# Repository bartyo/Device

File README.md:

# Device Work & Study Repository

This repository is a cluster of all work and studies concerning the wearable device of th Follow.ER project.

*Currently into this repository :*

- Prototype design an testing

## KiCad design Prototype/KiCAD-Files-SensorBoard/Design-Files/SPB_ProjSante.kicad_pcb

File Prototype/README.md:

# Prototype

## Current Status
Building the Adafruit nRF52 base code / Check the SPB solders

## Summary

This folder contains the files and studies that have been made to build a prototype design of the wearable device.

+ Follow.ER Goals
+ Global Architecture
+ Device Architecture
+ Device Prototype Goals
+ Elements
  + The MCU
  + The Sensors HUB

## Follow.ER Goals

 Follow.ER is a project that wants to build an easy patients-monitoring system for the ER thanks to wearable devices following thoses rules :
 
 - Able to follow Oximetry , HeartBeat and Localisation  (+ optionnal data)
 - Easy to Use
 - Safe
 - Costless

## Global Architecture

The Follow.ER system consist of wearables devices following patients in a mesh-designed BLE network. This allow centralized server management, distant access to data trough a WebApp and patient localisation (by BLE meshing & proximity)

## Device Architecture

The device system is a wearable sensor hub dedicated to Oximetry and Heartbeat measurement (+ optionnal Temperature or Movements). The system should be able to transmit trustful data, alarms and identifications thanks to the [BLE protocol]() in a secure way (ex: crypto).

## Device Prototype Goals

Before strating the "industry compatible" final designs, we need to be able to build a Proof of Concept to ensure that all the things we want to deploy is possible to realise. And so :

 - Being able to gather oximetry and pulse form transmissive or reflective measurement
 - Being able to tramsit data via BLE in a secure way 
 - Reach a current consumption level compatible with a wearable device

## Elements

The Device Prototype System (DPS) is make of two elements :

 - A MCU able to transmit trought BLE
 - A sensors HUB board able to return the targeted data and more if needed. 
 
 This system could be displayed as :

### The MCU => Feather nRF52 BlueFruit LE (Adafruit BLE)

The Feather nRF52 Bluefruit LE , from Adafruit Industires have been choosen because it allow to deploy an embedded BLE solution in a simple way (Arduino IDE compatible + breadboard pinout).

#### Board PinOut

The board PinOut can be found [HERE](https://learn.adafruit.com/bluefruit-nrf52-feather-learning-guide/device-pinout)

> The pin attributions could be found into the code and can be easily changed.

#### Protoype Code Architecure

The Prototype Code is based on a "TOKEN" system.

The user, via BLE or UART will send a 3 letters TOKEN that will tell the MCU the action to perform.
For exemple, ``BLK`` will cause the built-in red led to blink 5 time for 2,5s (a token table is indicated in the code and later in the docs).

That system allow an user to simply test methods and functions thanks to single instructions. Consequently, the softawre is constantly waiting for new tokens to follow. 

If a wrong token or an other situation trigger an error (variable ``done`` == ``false`` ), the system will send a message trough the selected communication protocol and set the token as ``NOP`` (do nothing) so user action can block the MCU.

Here's the architecture :

And here's the ***current*** TOKEN table (add new one if needed):

|TOKEN|Action|Need to send opt. Data ?|
|:--:|:--:|:--:|
|``NOP``|Do nothing| No |
|``ERR``|Raise an error (test func)| No |
|``BLK``|Do nothing| No |
|``OXI``|Gather Oximetry Data (single)| No |
|``OXB``|Gather Oximetry Data (buffered)| No |
|``TMP``|Gather Die Temperature| No |
|``MOD``|Switch the communication mode (BLE/UART)| No |
|``HWP``|Switch the hardawre interaction mode (SIMULATED/GPIOs)| No |
|``PTS``|Set the number of point to gather in buffered mode| Yes (16bit HEXA, ex: AF55)|
|``SMP``|Set the chip sampling frequency| Yes (8bit HEXA, ex: F5)|
|``AMP``|Set the chip range| Yes (8bit HEXA, ex: 08)|
|``PUL``|Set the chip pulse width| Yes (8bit HEXA, ex: A3)|
|``INT``|Set the chip/led current consumption| Yes (8bit HEXA, ex: 30)|

> For the Hexa values, look at the MAX30101 datasheet :) (the soft should take care of the rest)

An exemple of UART prototyping control:

### The Sensors HUB => Sensor Prototype Board (SPB)

To allow us to prototype with oximetry measurement, **we've built a Sensors Prototype Board** that gather **oximetry signal** by **reflectance method**. The chip is also able to send **die temperature measurements**.

In addition, we choose to put **two current measurement channels** so we should be able to **plot consumption curves** during the system study and reach better programming solution if needed.

Of course, the eletronical environnement is designed for a bug free use (I2C pull-up , decoupling resistors, voltage regulation, etc..)

The board B.O.M and the GERBER files could be found [HERE](https://github.com/ProjSante/Device/tree/master/Prototype/KiCAD-Files-SensorBoard)

The simplified board architecture could be displayed as :

#### SPB PinOut

> /!\ The input voltage should be 3.3v if you just want to use the Red and the IR LED; 5v if you want to use the Red, the IR and the Green LED

> Current measurement : Current_Analog or Current_Digital (in Volts) / 2000 =** ***Real Current*** (ex: 1V == 0.5mA)

To avoid ESB hazards, a protection could be put over the board thanks to the 4 fixation holes :

#### I2C methods

See the [MAX30101 Datasheet](https://datasheets.maximintegrated.com/en/ds/MAX30101.pdf)

|**Function**|Adress|Effects|Main Direction|
|:------:|:----:|:-----:|:-----:|
| Interrupt enable 1 | 0x02 | Use the bit 7 to 5 to set the interrupt conditions about dataflow | Write |
| Interrupt enable 2 | 0x03 | Use the bit 1 to set the interrupt condition about die temperature| Write |
| FIFO Write Pointer | 0x04 | Last data adress location , bytes 4 to 0 | Read |
| OF Counter | 0x05 | Overflow counter (if FIFO Full) , bytes 4 to 0 | Read |
| FIFO Read Pointer | 0x06 | I2C read adress location , bytes 4 to 0 | Read & Write |
| FIFO Data Register | 0x07 | Pointed data register (not always auto-incremented), 3x1 byte for one channel| Read |
| FIFO Config| 0x08 | Averaging [7:5] , FIFO RollOver Enable [4] , FIFO status when almost full [3:0] | Read & Write |
| Mode Config| 0x09 | Shutdown (register keeped and Int==0) [7] , Reset [6] , Measurement Mode [2:0] | Write |
| SpO2 Config| 0x0A | ADC Range [6:5] , Sample Rate [4:2] , Pulse Width [1:0] | Write |
| LED 1 Amplitude | 0x0C | 1 full byte (see datasheet) | Write |
| LED 2 Amplitude | 0x0D | 1 full byte (see datasheet) | Write |
| Temperature (Int) | 0x1F | 1 full byte (ex : the 12 in 12.5) | Read |
| Temperature (Fractional) | 0x20 | bit 4 to 0 (ex: the 0.5 in 12.5) | Read |
| Temperature Config | 0x21 | Use the bit 0 to enable die temperature measurment| Read |

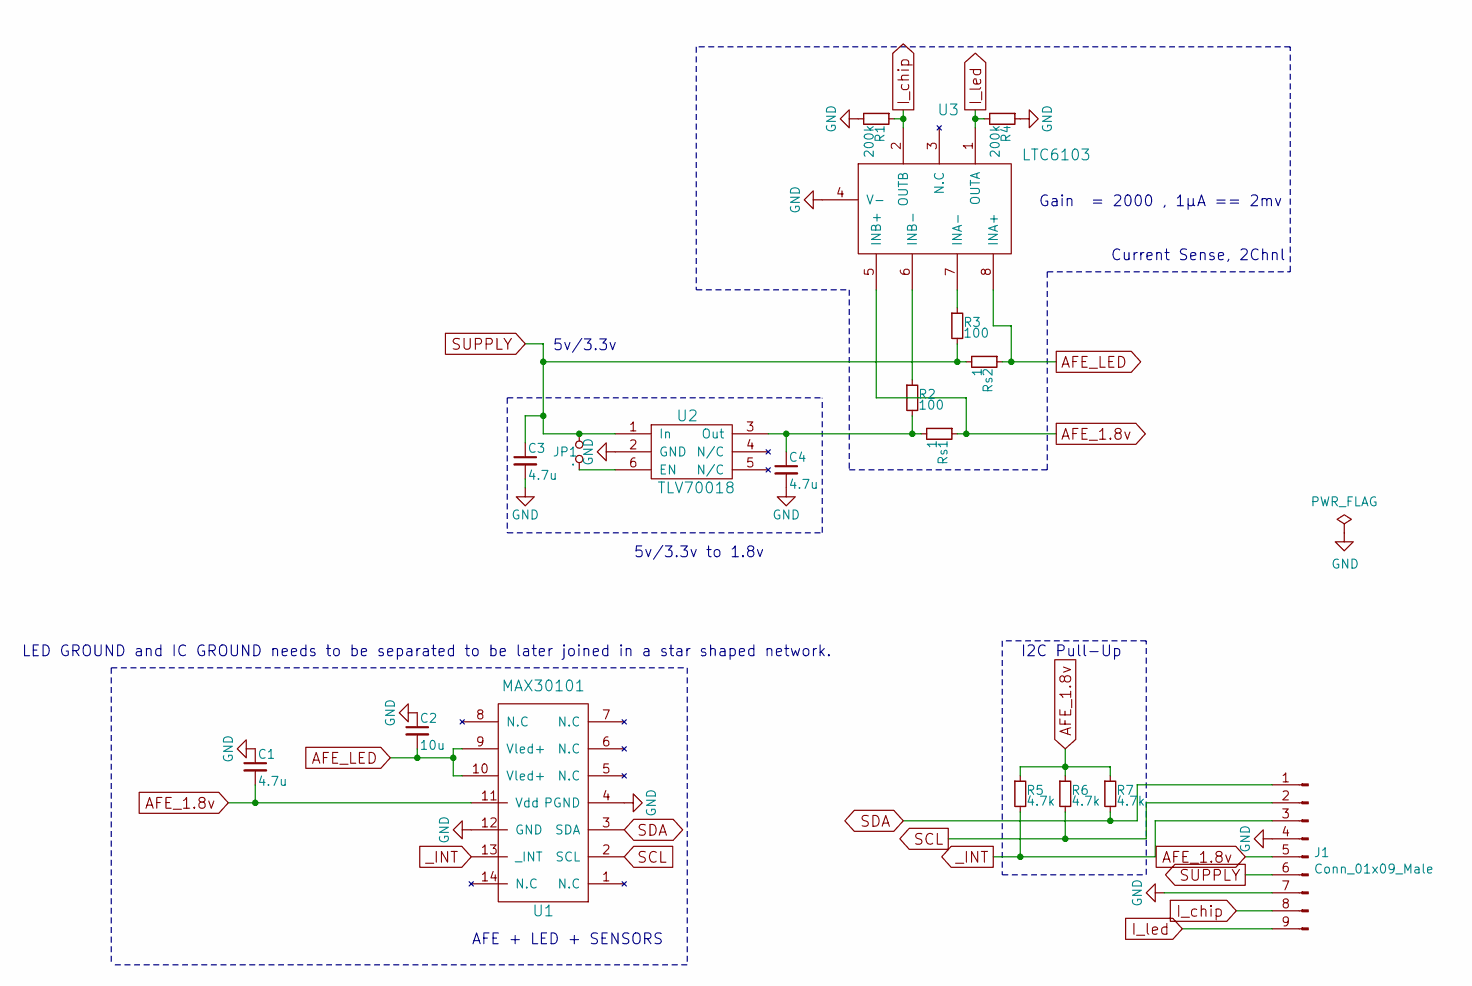
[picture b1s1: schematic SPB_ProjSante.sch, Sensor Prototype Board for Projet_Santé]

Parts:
C1, C3, C4: 4.7u; C_0402_1005Metric
C2: 10u; C_0603_1608Metric
J1: Conn_01x09_Male; PinHeader_1x09_P2.54mm_Vertical
JP1: .; C_0402_1005Metric
R1, R4: 200k; R_0402_1005Metric
R2, R3: 100; R_0402_1005Metric
R5, R6, R7: 4.7k; R_0402_1005Metric
Rs1, Rs2: 1; R_0603_1608Metric
U1: MAX30101; F134
U2: TLV70018; WSON-6_1.5x1.5mm_P0.5mm
U3: LTC6103; TSSOP-8_3x3mm_P0.65mm

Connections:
AFE_1.8v: C1.2, J1.5, R5.1, R6.1, R7.1, Rs1.1, U1.11 (Vdd), U3.5 (INB+)
AFE_LED: C2.2, Rs2.1, U1.9 (Vled+), U1.10 (Vled+), U3.8 (INA+)
GND: C1.1, C2.1, C3.2, C4.2, J1.4, J1.7, R1.2, R4.1, U1.4 (PGND), U1.12 (GND), U2.2 (GND), U3.4 (V-)
I_chip: J1.8, R1.1, U3.2 (OUTB)
I_led: J1.9, R4.2, U3.1 (OUTA)
unnamed: C4.1, R2.2, Rs1.2, U2.3 (Out)
unnamed: JP1.1, U2.6 (EN)
unnamed: R2.1, U3.6 (INB-)
unnamed: R3.1, U3.7 (INA-)
SCL: J1.2, R6.2, U1.2 (SCL)
SDA: J1.1, R7.2, U1.3 (SDA)
SUPPLY: C3.1, J1.6, JP1.2, R3.2, Rs2.2, U2.1 (In)
_INT: J1.3, R5.2, U1.13 (_INT)

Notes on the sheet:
I2C Pull-Up
Gain = 2000 , 1µA == 2mv
Current Sense, 2Chnl
5v/3.3v to 1.8v
5v/3.3v
AFE + LED + SENSORS
LED GROUND and IC GROUND needs to be separated to be later joined in a star shaped network.

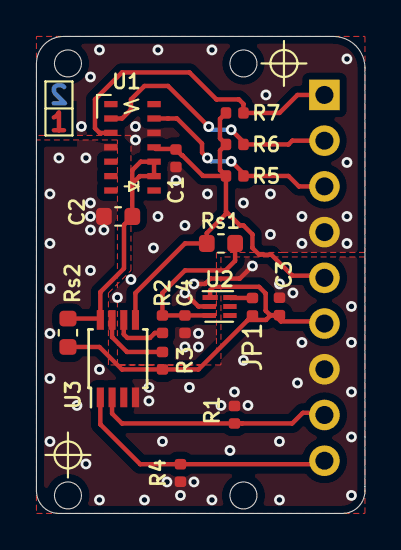
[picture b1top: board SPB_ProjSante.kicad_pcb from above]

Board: 2 copper layers, 18.2 x 26.5 mm, 18 parts (1 on the bottom side), 13 nets.

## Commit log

2019-10-11 Rename Prototype/KiCAD-Files-SensorBoard/DETAILS.md to Prototype/KiCAD-Files-SensorBoard/Design-Files/DETAILS.md
2019-10-11 Create LICENSE
2019-10-21 Latest Build - Basic Structure
2019-10-23 Lots of stuffs
    Token functions + COM functions + Simulated GPIOs + Defines + Chip init.
    Still need to add :
    - I2C Init and Bluetooth init
    - BLE and GPIO alternatives
2019-10-23 Added Issue warning
2019-10-24 Compact code, I2C Added, Setting TOKENS possible
2019-10-29 Hotfix + Buffer variable (SIZEx6bytes wide)
